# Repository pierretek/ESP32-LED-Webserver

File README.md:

# ESP32 LED Webserver &nbsp; 

An asynchronous webserver hosted on an ESP32 that controls an array of four LEDs using a browser based terminal interface
 
## Details 
- Main program is in `src/main.cpp`, project libraries are in `lib/` and the web interface is in `data/`.
- The ESP32 hosts an asynchronous webserver that recieves commands and periodically sends watchdog signals
- Check out the [demo page!](https://pierretek.github.io/ESP32-LED-Webserver/)

## Requirements 

### Hardware
- `ESP32 WROOM 32`
- Four uniquely colored `LEDs`
- Four `220Ω` resistors
- Breadboard and connector wires
### Software
- VS Code with the platformIO extension

## How to Use
1. Build the simple circuit below with the components listed above:

2. Import the project folder in **VS Code** with **platformIO** (platformio.ini must be in root)
3. Navigate to `src/main.cpp` and fill in your WIFI details (lines 8-13)
4. From the plugins bar, navigate to `PlatformIO > Upload Filesystem Image`, and run it to upload the website to the esp32
5. Connect your ESP32 via USB and upload the project
6. Open the serial monitor and connect to the IP mentioned using your browser
7. Send commands via the terminal interface and enjoy! 

## Possible Commands
```
led red 100ms ⇒ Turns on red LED for 100ms 
led blue 10s blink ⇒ Repeatedly blinks blue LED every 10s
led all 5 ⇒ Turns on all LEDs for 5s 
led all 2 blink ⇒ Repeatedly blinks all LEDs every 2s
led all 1s pattern ⇒ Blinks the LEDs  a staggered offset pattern every 1s
```

## Bonus
Although **completely** redundant and unnecessary, I also decided to make a simple PCB for fun and to free up my breadboard for other projects. I made the PCB in KiCAD and the project files can be found under `PCBFiles/`.

### PCB Photos

### Demo with PCB
https://github.com/user-attachments/assets/332d59a1-b7c1-4675-94df-a39690c8915f

---
_thanks for reading_

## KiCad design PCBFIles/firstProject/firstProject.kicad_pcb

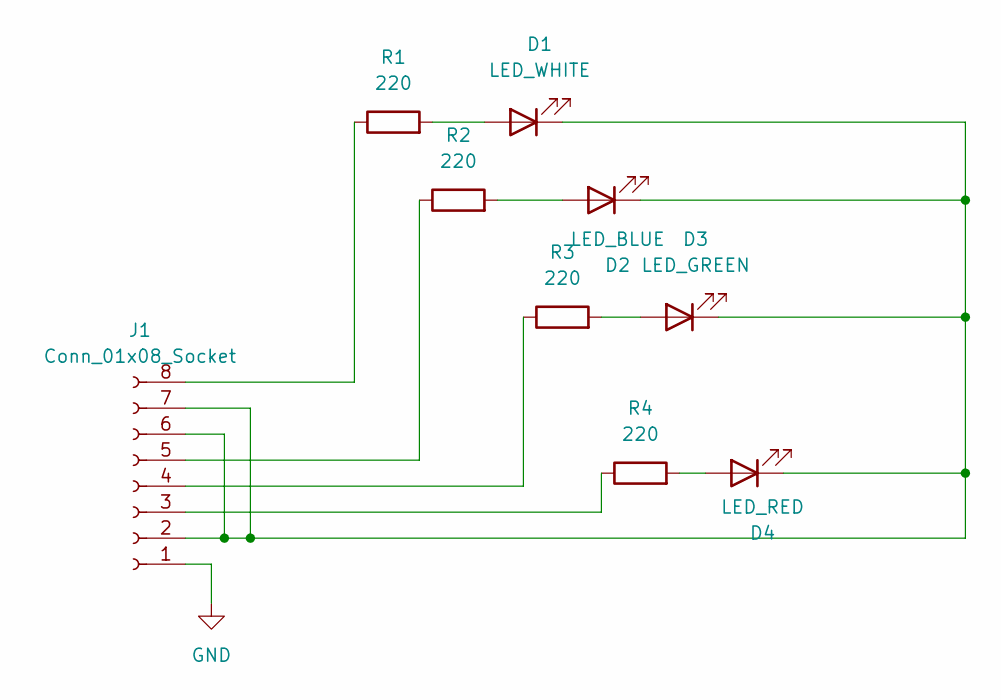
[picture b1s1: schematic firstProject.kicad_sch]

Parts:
D1: LED_WHITE; LED_D5.0mm
D2: LED_BLUE; LED_D5.0mm
D3: LED_GREEN; LED_D5.0mm
D4: LED_RED; LED_D5.0mm
J1: Conn_01x08_Socket; PinSocket_1x08_P2.54mm_Vertical
R1, R2, R3, R4: 220; R_Axial_DIN0204_L3.6mm_D1.6mm_P5.08mm_Horizontal

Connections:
GND: J1.1
unnamed: D1.2 (A), R1.2
unnamed: D1.1 (K), D2.1 (K), D3.1 (K), D4.1 (K), J1.2, J1.6, J1.7
unnamed: D2.2 (A), R2.2
unnamed: D3.2 (A), R3.2
unnamed: D4.2 (A), R4.2
unnamed: J1.3, R4.1
unnamed: J1.4, R3.1
unnamed: J1.5, R2.1
unnamed: J1.8, R1.1

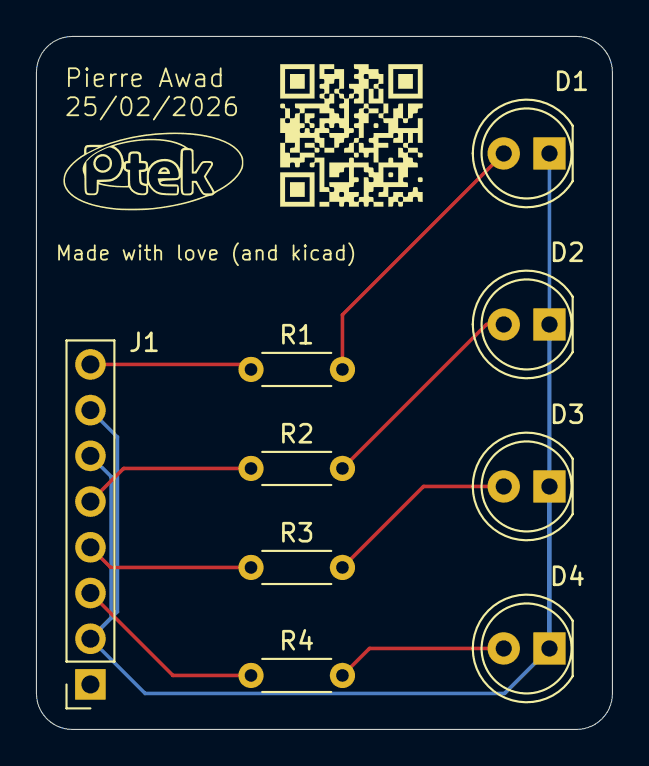
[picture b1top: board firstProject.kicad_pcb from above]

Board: 2 copper layers, 32.0 x 38.5 mm, 9 parts (0 on the bottom side), 9 nets.

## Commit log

2026-02-04 add functional static website
2026-02-18 completed button based website
2026-02-22 convert button based website to terminal based one
2026-03-04 completed entire project
2026-03-04 attempt to host the web interface on github pages
2026-03-04 Add demo page link to README
2026-03-04 update the github command
2026-03-04 fix connection status being true for no reason
2026-03-06 small changes to terminal commands and README formatting
2026-03-06 more readme changes
2026-03-06 even more readme changes
2026-03-06 reverting the last two commits cuz they didnt do anything
2026-03-09 update README title formatting
2026-03-09 Improve README with circuit diagram and steps
2026-03-09 fix instruction steps
2026-03-11 adding PCB files and adjusting the LED pin positions
2026-03-11 add demo video and pcb images to README
2026-03-11 reformatted possible commands section in readme
2026-03-11 Fix typo in README
